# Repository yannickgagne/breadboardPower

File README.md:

# breadboardPower
Breadboard Power Supply

Simple breadboard power supply with 3.3V, 5V and 12V ouput.

Can provide two different voltage at the same time to different rails.

I know it could have been way smaller with more SMD components but I wanted to use what I had on hand.

https://oshpark.com/shared_projects/d1cXCggO

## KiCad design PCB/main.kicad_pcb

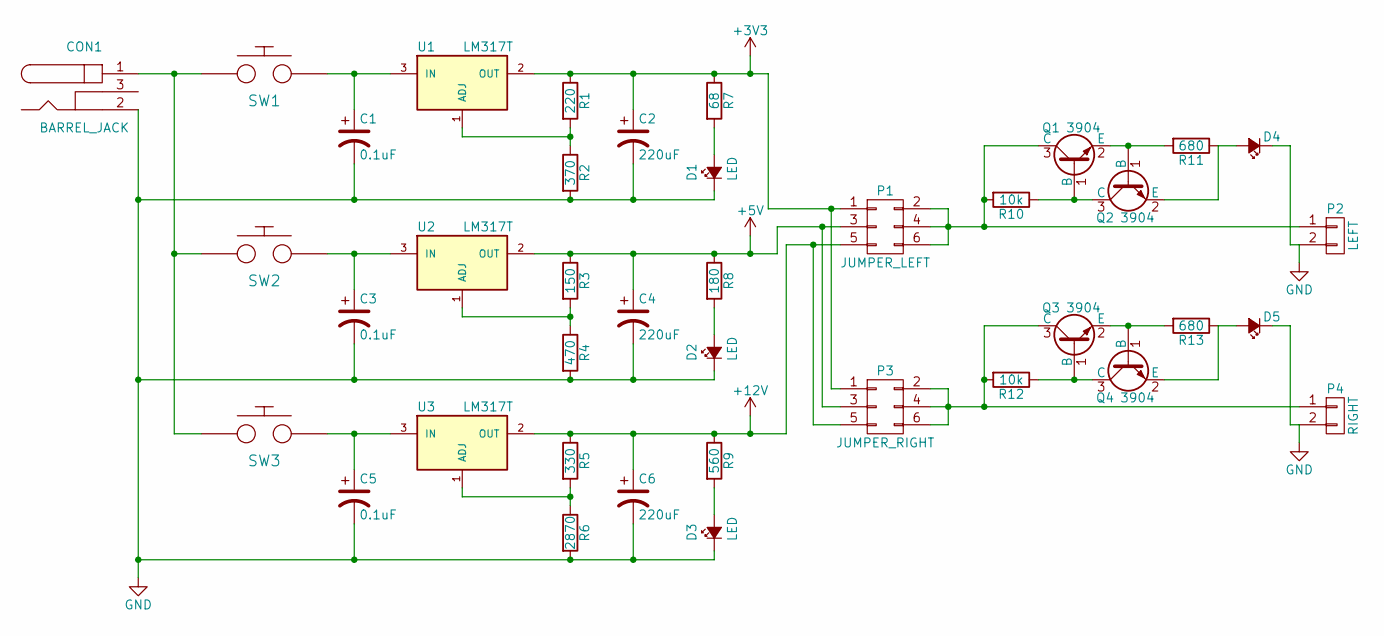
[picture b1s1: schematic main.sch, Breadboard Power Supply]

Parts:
C1, C3, C5: 0.1uF; C_Radial_D5_L11_P2
C2, C4, C6: 220uF; C_Radial_D6.3_L11.2_P2.5
CON1: BARREL_JACK; BARREL_JACK2
D1, D2, D3: LED; LED_0805
D4, D5: Led_Small; LED_0805
P1: JUMPER_LEFT; Pin_Header_Straight_2x03
P2: LEFT; Pin_Header_Straight_1x02
P3: JUMPER_RIGHT; Pin_Header_Straight_2x03
P4: RIGHT; Pin_Header_Straight_1x02
Q1, Q2, Q3, Q4: 3904; SOT-23
R1: 220; Resistor_Horizontal_RM7mm
R2: 370; Resistor_Horizontal_RM7mm
R3: 150; Resistor_Horizontal_RM7mm
R4: 470; Resistor_Horizontal_RM7mm
R5: 330; Resistor_Horizontal_RM7mm
R6: 2870; Resistor_Horizontal_RM7mm
R7: 68; Resistor_Horizontal_RM7mm
R8: 180; Resistor_Horizontal_RM7mm
R9: 560; Resistor_Horizontal_RM7mm
R10, R12: 10k; Resistor_Horizontal_RM7mm
R11, R13: 680; Resistor_Horizontal_RM7mm
SW1, SW2, SW3: 12x12_PUSHBUTTON_SPST
U1, U2, U3: LM317T; TO-220

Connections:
+3V3: C2.1, P1.1, P3.1, R1.1, R7.1, U1.2 (OUT)
+5V: C4.1, P1.3, P3.3, R3.1, R8.1, U2.2 (OUT)
+12V: C6.1, P1.5, P3.5, R5.1, R9.1, U3.2 (OUT)
GND: C1.2, C2.2, C3.2, C4.2, C5.2, C6.2, CON1.2, D1.1 (K), D2.1 (K), D3.1 (K), D4.1 (K), D5.1 (K), P2.2, P4.2, R2.2, R4.2, R6.2
unnamed: C1.1, SW1.2, U1.3 (IN)
unnamed: C3.1, SW2.2, U2.3 (IN)
unnamed: C5.1, SW3.2, U3.3 (IN)
unnamed: CON1.1, SW1.1, SW2.1, SW3.1
unnamed: D1.2 (A), R7.2
unnamed: D2.2 (A), R8.2
unnamed: D3.2 (A), R9.2
unnamed: D4.2 (A), Q2.2 (E), R11.1
unnamed: D5.2 (A), Q4.2 (E), R13.1
unnamed: P1.2, P1.4, P1.6, P2.1, Q1.3 (C), R10.2
unnamed: P3.2, P3.4, P3.6, P4.1, Q3.3 (C), R12.2
unnamed: Q1.1 (B), Q2.3 (C), R10.1
unnamed: Q1.2 (E), Q2.1 (B), R11.2
unnamed: Q3.1 (B), Q4.3 (C), R12.1
unnamed: Q3.2 (E), Q4.1 (B), R13.2
unnamed: R1.2, R2.1, U1.1 (ADJ)
unnamed: R3.2, R4.1, U2.1 (ADJ)
unnamed: R5.2, R6.1, U3.1 (ADJ)

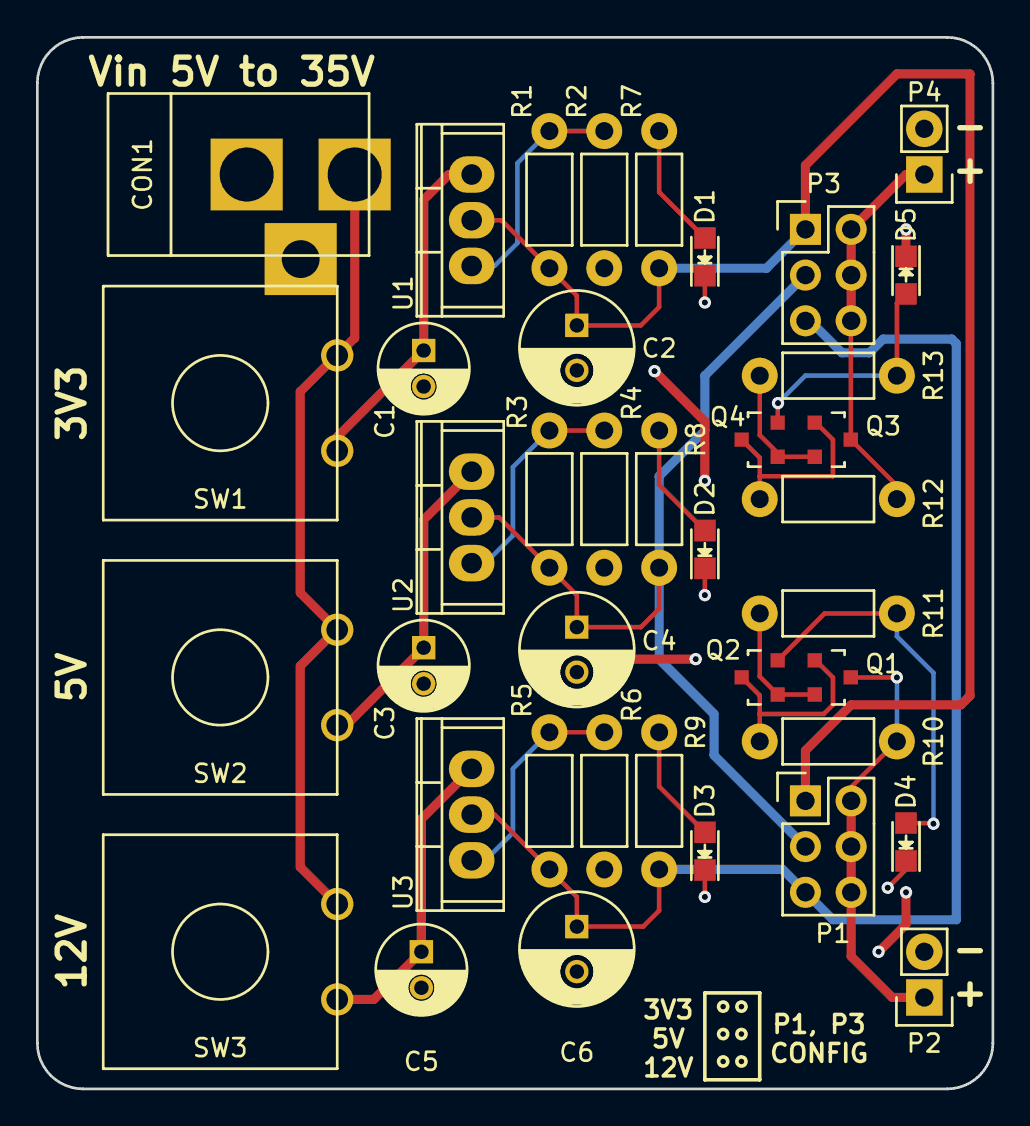
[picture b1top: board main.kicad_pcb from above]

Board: 2 copper layers, 53.1 x 58.4 mm, 39 parts (0 on the bottom side), 22 nets.

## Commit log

2016-04-13 :neckbeard: Added .gitattributes
2016-04-14 led output circuit
2016-04-15 begin pcb layout
2016-04-15 layout
2016-04-15 before traces
2016-04-16 traces again
2016-04-17 edge cuts and oshpark settings
2016-04-18 real switches and oshpark test
2016-04-18 pcb powa!
2016-04-19 smaller pcb
2016-04-19 edge cut fix
2016-04-19 output pins
2016-04-19 added to top silk screen
2016-04-20 fat holes for barrel jack
2016-04-25 hopefully last pcb layout
2016-04-25 again...
2016-04-25 oshpark renders
2016-04-26 battery doc
2016-04-27 barrel jack footprint tuning
2016-04-28 submitted to oshpark :anguished:
    praying for a working PCB!!!
2016-04-28 cleanup and oshpark renders :+1:
2016-05-18 Some pads hole size modification.
2016-05-19 added jumper for disconnected ground plane section
2019-03-17 Confirmed all v0.2 mods
2019-03-17 updated oshpark link.
2019-03-17 typos
